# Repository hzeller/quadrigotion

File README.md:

Quadrigotion: Multiple Motor Drivers, one connector
============================================================

Often it is useful to have all the motor drivers needed for a machine
on a separate circuit board to be able to mount it to a heatsink or close
to the action. This is what this project is about.
The name **Quadrigotion** is a word amalgamated from 'Quadriga' (Four
horses powering a chariot) and 'Motion'.

Motivation for this project to have motor drivers easily replacable and
testable on my various 3D printers and CNC machines. Since I am also
[developing motion control software][BeagleG], I might have an unusual
high demand for this :)

The idea is to have a common connector type, described below, and various
implementations of that concept. The first implementation is using a TMC2660,
which is the 'big brother' of the more well-known TMC2100.

Other implementations are conceivable e.g. with Pololu modules, DRV8825, or
super high current and voltage drivers for heavy CNC machines.
Implementations can be super bare-bone and not use the SPI connection or
could be configured via SPI using a shift-register and digital potentiometers
if the chips can't be configured with SPI directly.
While the first Quadrigotion implementation happens to also have four motor
drivers, this could of course extend in the future.

The Connector
--------------

The digital input is provided with an IDC connector with 16 pins (2x8) or
20 pins (2x10).
It features a SPI bus to send configuration data and also read motor/driver
status (the actual protocol is of implementation-dependent, but they all can
share the same hardware interface).

| Desc               | Pin | Pin | Desc
|-------------------:|:---:|:---:|:-----------------------------
|               GND  |   1 |   2 | VCC (3.3V-5V)
| All Motors ~Enable |   3 |   4 | (not connected; reserved for fault-out)
|          ~CS (SPI) |   5 |   6 | CLK (SPI)
|         MISO (SPI) |   7 |   8 | MOSI (SPI)
|            Step #1 |   9 |  10 | Dir #1
|            Step #2 |  11 |  12 | Dir #2
|            Step #3 |  13 |  14 | Dir #3
|            Step #4 |  15 |  16 | Dir #4 -------- END IDC 16 variant
|            Step #5 |  17 |  18 | Dir #5
|            Step #6 |  19 |  20 | Dir #6 -------- END IDC 20 variant

It is easy to see that extending the driver count would just require a wider
IDC connector; the serial configuration interface can deal with any
number. A 16 pin IDC connector allows for 4 steppers, the next configuration
with 20 pins would allow for six drivers.

A single Enable-pin is provided that affects all drivers. This makes it easy
to wire up that signal directly e.g. for emergency buttons.
If more individual control of each driver is needed, this can be done via
the SPI connection.

The fast signals for each stepper, step and dir, are provided in
a parallel input with two lines per stepper.

A Quadrigotion connector has a single ChipSelect signal; multiple drivers
on each implementation have to share that bus, e.g. by internally being
organized as a shift register that latches when ~CS goes high again.

One pin (pin 4) is not connected yet, but it is reserved for fault detection
output (e.g stalling, overheating or over-current).

In an upcoming project, I'll build a breakout board to work with [BeagleG].

TMC2660 Implementation
----------------------

The first implementation is based on the TMC2660, a feature-rich motor driver
that can drive up to 4A (2.8A RMS). The 40mmx125mm PCB is a four layer board
which duals as heat conductor for cooling. Multiple M2.5 mounting holes allow
to firmly mount it to a heatsink and get even pressure to individual silicone
heatsink pads.
Power is provided via a 4-pin JST VH connector (3.96mm pitch),
circuit protected with an automotive ATC Mini 297 blade fuse.

You find the gerbers in the [fab/](./fab) directory. Board is also
[shared on OshPark]. Cave: since this is the very first version, no
testing has been done yet with a physical board.

[BeagleG]: https://github.com/hzeller/beagleg
[shared on OshPark]: https://oshpark.com/shared_projects/M0SQCRdL

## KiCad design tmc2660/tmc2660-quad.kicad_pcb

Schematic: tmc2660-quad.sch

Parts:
F1: Fuse; BladeFuse-Mini_Keystone-3586
J1: Power; JST_VH_B4PS-VH_2x4x3.96mm_Horizontal
J2: DataIn; IDC_Header_SMD_16pins
M0: Mount; MountingHole_2.7mm_M2.5
M1: Mount; MountingHole_2.7mm_M2.5_Pad

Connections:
/PowerIn: F1.2, J1.1, J1.2
CS: J2.5; also elsewhere on the board
DIR1: J2.10; also elsewhere on the board
DIR2: J2.12; also elsewhere on the board
DIR3: J2.14; also elsewhere on the board
DIR4: J2.16; also elsewhere on the board
GLOBAL_MISO: J2.7; also elsewhere on the board
GLOBAL_MOSI: J2.8; also elsewhere on the board
GND: J1.3, J1.4, J2.1, M1.1; also elsewhere on the board
SCLK: J2.6; also elsewhere on the board
STEP1: J2.9; also elsewhere on the board
STEP2: J2.11; also elsewhere on the board
STEP3: J2.13; also elsewhere on the board
STEP4: J2.15; also elsewhere on the board
VCC: J2.2; also elsewhere on the board
VMot: F1.1; also elsewhere on the board
~ENABLE: J2.3; also elsewhere on the board

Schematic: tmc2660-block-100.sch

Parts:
C100, C101: 10n; C_0603
C102, C103: 10u; C_1206; Voltage 50V; DigiKey 1276-6736-1-ND
C104, C106: 100n; C_0805; Voltage >= 16V; DigiKey 1276-2450-2-ND
C105: 100n; C_0805; Voltage 50V; DigiKey 1276-2450-2-ND
C107: 180u; CP_Radial_D8.0mm_P3.50mm; Voltage 35V; DigiKey 565-3911-ND
C108: 470n; C_0603; Voltage 16V
J100: 0R; R_0603
M100: Mount; MountingHole_2.7mm_M2.5
M101: Mount; MountingHole_2.7mm_M2.5_Pad
P100: Motor; JST_XH_B04B-XH-A_04x2.50mm_Straight
R100, R101: 0.075; R_2512; DigiKey CSRN2512FK75L0CT-ND
R102, R103: 10R; R_0603
U100: TMC2660; LQFP-44_10x10mm_Pitch0.8mm

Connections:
/TMC2660-100/A1: P100.2, U100.2 (OA1), U100.3 (OA1), U100.7 (OA1), U100.8 (OA1)
/TMC2660-100/A2: P100.1, U100.5 (OA2), U100.6 (OA2), U100.10 (OA2), U100.11 (OA2)
/TMC2660-100/B1: P100.3, U100.26 (OB1), U100.27 (OB1), U100.31 (OB1), U100.32 (OB1)
/TMC2660-100/B2: P100.4, U100.23 (OB2), U100.24 (OB2), U100.28 (OB2), U100.29 (OB2)
/TMC2660-100/BRA: R101.1, R103.2, U100.9 (BRA)
/TMC2660-100/BRB: R100.1, R102.1, U100.25 (BRB)
/TMC2660-100/VHS: C104.2, U100.35 (VHS)
/TMC2660-200/MISO: J100.2, U100.15 (MOSI); also elsewhere on the board
CS: U100.18 (~CS); also elsewhere on the board
DIR1: U100.41 (DIR); also elsewhere on the board
GLOBAL_MISO: U100.14 (MISO); also elsewhere on the board
GLOBAL_MOSI: J100.1; also elsewhere on the board
GND: C100.1, C101.2, C102.2, C103.2, C105.2, C106.2, C107.2, C108.2, M101.1, R100.2, R101.2, U100.1 (NC), U100.17 (GND), U100.21 (CLK), U100.39 (GND), U100.44 (GND); also elsewhere on the board
unnamed: C100.2, R102.2, U100.22 (SRB)
unnamed: C101.1, R103.1, U100.12 (SRA)
unnamed: C108.1, U100.13 (5VOUT)
SCLK: U100.16 (SCLK); also elsewhere on the board
STEP1: U100.42 (STEP); also elsewhere on the board
VCC: C106.1, U100.40 (VCC); also elsewhere on the board
VMot: C102.1, C103.1, C104.1, C105.1, C107.1, U100.4 (VSA), U100.30 (VSB), U100.33 (NC), U100.36 (VS); also elsewhere on the board
~ENABLE: U100.19 (~EN); also elsewhere on the board

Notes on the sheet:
Jumper on highest popuplated
Sense Resistors alternatively also with 100mOhm

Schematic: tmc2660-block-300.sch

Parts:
C300, C301: 10n; C_0603
C302, C303: 10u; C_1206; Voltage 50V; DigiKey 1276-6736-1-ND
C304, C306: 100n; C_0805; Voltage >= 16V; DigiKey 1276-2450-2-ND
C305: 100n; C_0805; Voltage 50V; DigiKey 1276-2450-2-ND
C307: 180u; CP_Radial_D8.0mm_P3.50mm; Voltage 35V; DigiKey 565-3911-ND
C308: 470n; C_0603; Voltage 16V
J300: 0R; R_0603
M300: Mount; MountingHole_2.7mm_M2.5
M301: Mount; MountingHole_2.7mm_M2.5_Pad
P300: Motor; JST_XH_B04B-XH-A_04x2.50mm_Straight
R300, R301: 0.075; R_2512; DigiKey CSRN2512FK75L0CT-ND
R302, R303: 10R; R_0603
U300: TMC2660; LQFP-44_10x10mm_Pitch0.8mm

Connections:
/TMC2660-300/A1: P300.2, U300.2 (OA1), U300.3 (OA1), U300.7 (OA1), U300.8 (OA1)
/TMC2660-300/A2: P300.1, U300.5 (OA2), U300.6 (OA2), U300.10 (OA2), U300.11 (OA2)
/TMC2660-300/B1: P300.3, U300.26 (OB1), U300.27 (OB1), U300.31 (OB1), U300.32 (OB1)
/TMC2660-300/B2: P300.4, U300.23 (OB2), U300.24 (OB2), U300.28 (OB2), U300.29 (OB2)
/TMC2660-300/BRA: R301.1, R303.2, U300.9 (BRA)
/TMC2660-300/BRB: R300.1, R302.1, U300.25 (BRB)
/TMC2660-300/MISO: U300.14 (MISO); also elsewhere on the board
/TMC2660-300/VHS: C304.2, U300.35 (VHS)
/TMC2660-400/MISO: J300.2, U300.15 (MOSI); also elsewhere on the board
CS: U300.18 (~CS); also elsewhere on the board
DIR3: U300.41 (DIR); also elsewhere on the board
GLOBAL_MOSI: J300.1; also elsewhere on the board
GND: C300.1, C301.2, C302.2, C303.2, C305.2, C306.2, C307.2, C308.2, M301.1, R300.2, R301.2, U300.1 (NC), U300.17 (GND), U300.21 (CLK), U300.39 (GND), U300.44 (GND); also elsewhere on the board
unnamed: C300.2, R302.2, U300.22 (SRB)
unnamed: C301.1, R303.1, U300.12 (SRA)
unnamed: C308.1, U300.13 (5VOUT)
SCLK: U300.16 (SCLK); also elsewhere on the board
STEP3: U300.42 (STEP); also elsewhere on the board
VCC: C306.1, U300.40 (VCC); also elsewhere on the board
VMot: C302.1, C303.1, C304.1, C305.1, C307.1, U300.4 (VSA), U300.30 (VSB), U300.33 (NC), U300.36 (VS); also elsewhere on the board
~ENABLE: U300.19 (~EN); also elsewhere on the board

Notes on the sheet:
Jumper on highest popuplated
Sense Resistors alternatively also with 100mOhm

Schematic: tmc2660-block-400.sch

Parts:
C400, C401: 10n; C_0603
C402, C403: 10u; C_1206; Voltage 50V; DigiKey 1276-6736-1-ND
C404, C406: 100n; C_0805; Voltage >= 16V; DigiKey 1276-2450-2-ND
C405: 100n; C_0805; Voltage 50V; DigiKey 1276-2450-2-ND
C407: 180u; CP_Radial_D8.0mm_P3.50mm; Voltage 35V; DigiKey 565-3911-ND
C408: 470n; C_0603; Voltage 16V
J400: 0R; R_0603
M400: Mount; MountingHole_2.7mm_M2.5
M401: Mount; MountingHole_2.7mm_M2.5_Pad
P400: Motor; JST_XH_B04B-XH-A_04x2.50mm_Straight
R400, R401: 0.075; R_2512; DigiKey CSRN2512FK75L0CT-ND
R402, R403: 10R; R_0603
U400: TMC2660; LQFP-44_10x10mm_Pitch0.8mm

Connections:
/TMC2660-400/A1: P400.2, U400.2 (OA1), U400.3 (OA1), U400.7 (OA1), U400.8 (OA1)
/TMC2660-400/A2: P400.1, U400.5 (OA2), U400.6 (OA2), U400.10 (OA2), U400.11 (OA2)
/TMC2660-400/B1: P400.3, U400.26 (OB1), U400.27 (OB1), U400.31 (OB1), U400.32 (OB1)
/TMC2660-400/B2: P400.4, U400.23 (OB2), U400.24 (OB2), U400.28 (OB2), U400.29 (OB2)
/TMC2660-400/BRA: R401.1, R403.2, U400.9 (BRA)
/TMC2660-400/BRB: R400.1, R402.1, U400.25 (BRB)
/TMC2660-400/MISO: U400.14 (MISO); also elsewhere on the board
/TMC2660-400/VHS: C404.2, U400.35 (VHS)
CS: U400.18 (~CS); also elsewhere on the board
DIR4: U400.41 (DIR); also elsewhere on the board
GLOBAL_MOSI: J400.1, J400.2, U400.15 (MOSI); also elsewhere on the board
GND: C400.1, C401.2, C402.2, C403.2, C405.2, C406.2, C407.2, C408.2, M401.1, R400.2, R401.2, U400.1 (NC), U400.17 (GND), U400.21 (CLK), U400.39 (GND), U400.44 (GND); also elsewhere on the board
unnamed: C400.2, R402.2, U400.22 (SRB)
unnamed: C401.1, R403.1, U400.12 (SRA)
unnamed: C408.1, U400.13 (5VOUT)
SCLK: U400.16 (SCLK); also elsewhere on the board
STEP4: U400.42 (STEP); also elsewhere on the board
VCC: C406.1, U400.40 (VCC); also elsewhere on the board
VMot: C402.1, C403.1, C404.1, C405.1, C407.1, U400.4 (VSA), U400.30 (VSB), U400.33 (NC), U400.36 (VS); also elsewhere on the board
~ENABLE: U400.19 (~EN); also elsewhere on the board

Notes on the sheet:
Jumper on highest popuplated
Sense Resistors alternatively also with 100mOhm

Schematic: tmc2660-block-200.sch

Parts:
C200, C201: 10n; C_0603
C202, C203: 10u; C_1206; Voltage 50V; DigiKey 1276-6736-1-ND
C204, C206: 100n; C_0805; Voltage >= 16V; DigiKey 1276-2450-2-ND
C205: 100n; C_0805; Voltage 50V; DigiKey 1276-2450-2-ND
C207: 180u; CP_Radial_D8.0mm_P3.50mm; Voltage 35V; DigiKey 565-3911-ND
C208: 470n; C_0603; Voltage 16V
J200: 0R; R_0603
M200: Mount; MountingHole_2.7mm_M2.5
M201: Mount; MountingHole_2.7mm_M2.5_Pad
P200: Motor; JST_XH_B04B-XH-A_04x2.50mm_Straight
R200, R201: 0.075; R_2512; DigiKey CSRN2512FK75L0CT-ND
R202, R203: 10R; R_0603
U200: TMC2660; LQFP-44_10x10mm_Pitch0.8mm

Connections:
/TMC2660-200/A1: P200.2, U200.2 (OA1), U200.3 (OA1), U200.7 (OA1), U200.8 (OA1)
/TMC2660-200/A2: P200.1, U200.5 (OA2), U200.6 (OA2), U200.10 (OA2), U200.11 (OA2)
/TMC2660-200/B1: P200.3, U200.26 (OB1), U200.27 (OB1), U200.31 (OB1), U200.32 (OB1)
/TMC2660-200/B2: P200.4, U200.23 (OB2), U200.24 (OB2), U200.28 (OB2), U200.29 (OB2)
/TMC2660-200/BRA: R201.1, R203.2, U200.9 (BRA)
/TMC2660-200/BRB: R200.1, R202.1, U200.25 (BRB)
/TMC2660-200/MISO: U200.14 (MISO); also elsewhere on the board
/TMC2660-200/VHS: C204.2, U200.35 (VHS)
/TMC2660-300/MISO: J200.2, U200.15 (MOSI); also elsewhere on the board
CS: U200.18 (~CS); also elsewhere on the board
DIR2: U200.41 (DIR); also elsewhere on the board
GLOBAL_MOSI: J200.1; also elsewhere on the board
GND: C200.1, C201.2, C202.2, C203.2, C205.2, C206.2, C207.2, C208.2, M201.1, R200.2, R201.2, U200.1 (NC), U200.17 (GND), U200.21 (CLK), U200.39 (GND), U200.44 (GND); also elsewhere on the board
unnamed: C200.2, R202.2, U200.22 (SRB)
unnamed: C201.1, R203.1, U200.12 (SRA)
unnamed: C208.1, U200.13 (5VOUT)
SCLK: U200.16 (SCLK); also elsewhere on the board
STEP2: U200.42 (STEP); also elsewhere on the board
VCC: C206.1, U200.40 (VCC); also elsewhere on the board
VMot: C202.1, C203.1, C204.1, C205.1, C207.1, U200.4 (VSA), U200.30 (VSB), U200.33 (NC), U200.36 (VS); also elsewhere on the board
~ENABLE: U200.19 (~EN); also elsewhere on the board

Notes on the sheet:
Jumper on highest popuplated
Sense Resistors alternatively also with 100mOhm

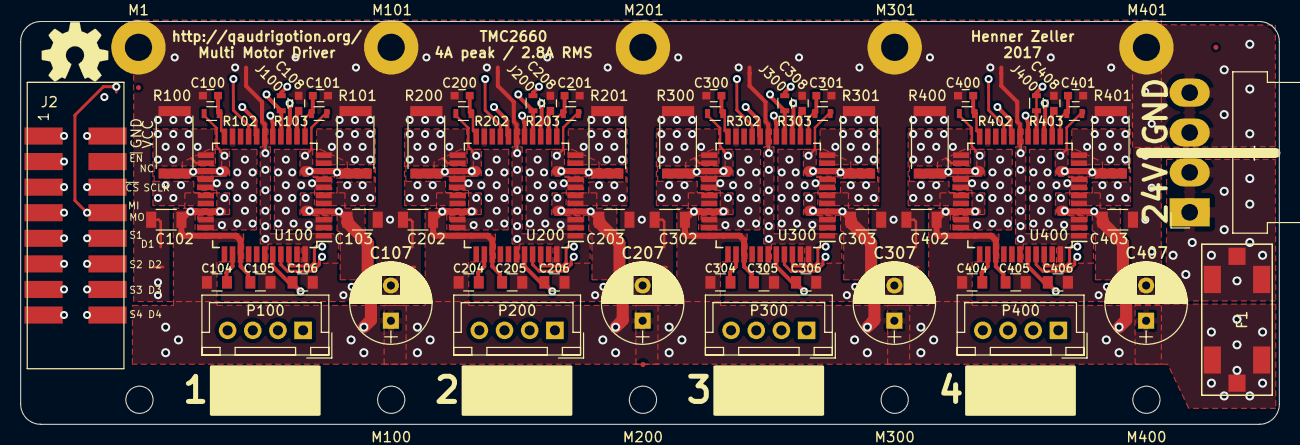
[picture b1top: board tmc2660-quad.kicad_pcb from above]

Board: 4 copper layers, 125.0 x 40.0 mm, 77 parts (0 on the bottom side), 60 nets.

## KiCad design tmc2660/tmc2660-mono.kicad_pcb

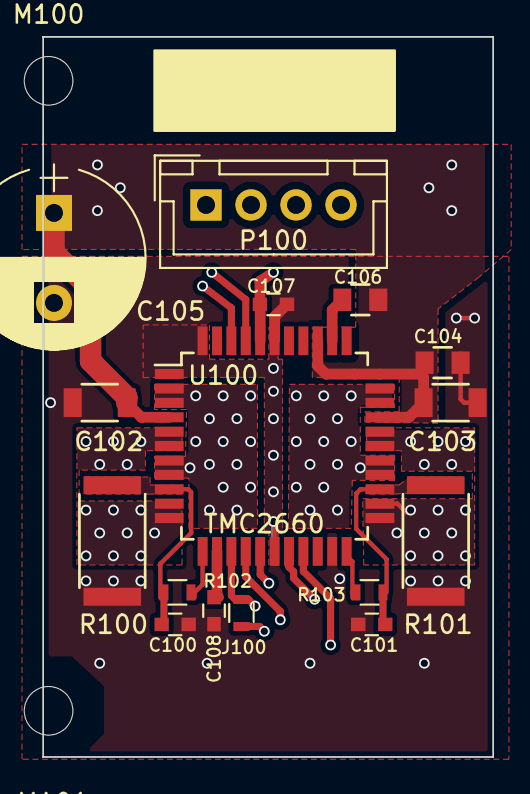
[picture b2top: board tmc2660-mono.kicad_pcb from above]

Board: 4 copper layers, 25.0 x 40.0 mm, 18 parts (0 on the bottom side), 14 nets.

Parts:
C100, C101: 10n; C_0603
C102, C103: 10u; C_1206
C104, C106: 100n; C_0805
C105: 100u; CP_Radial_D10.0mm_P5.00mm
C107: 100n; C_0603
C108: 470n; C_0603
J100: 0R; R_0603
M100, M101: Mount; MountingHole_2.7mm_M2.5
P100: Motor; JST_XH_B04B-XH-A_04x2.50mm_Straight
R100, R101: 0.075; R_2512
R102, R103: 10R; R_0603
U100: TMC2660; LQFP-44_10x10mm_Pitch0.8mm

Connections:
/TMC2660-Block/A1: P100.2, U100.2, U100.3, U100.7, U100.8
/TMC2660-Block/A2: P100.1, U100.5, U100.6, U100.10, U100.11
/TMC2660-Block/B1: P100.3, U100.26, U100.27, U100.31, U100.32
/TMC2660-Block/B2: P100.4, U100.23, U100.24, U100.28, U100.29
/TMC2660-Block/BRA: C100.2, R100.1, R102.2, U100.9
/TMC2660-Block/BRB: C101.1, R101.1, R103.1, U100.25
/TMC2660-Block/MISO: J100.2, U100.14
GND: C100.1, C101.2, C102.2, C103.2, C104.2, C105.2, C107.2, C108.2, R100.2, R101.2, U100.1, U100.17, U100.21, U100.39, U100.44
unnamed: C106.2, U100.35
unnamed: C108.1, U100.13
unnamed: R102.1, U100.12
unnamed: R103.2, U100.22
VCC: C107.1, U100.40
VMot: C102.1, C103.1, C104.1, C105.1, C106.1, U100.4, U100.30, U100.33, U100.36

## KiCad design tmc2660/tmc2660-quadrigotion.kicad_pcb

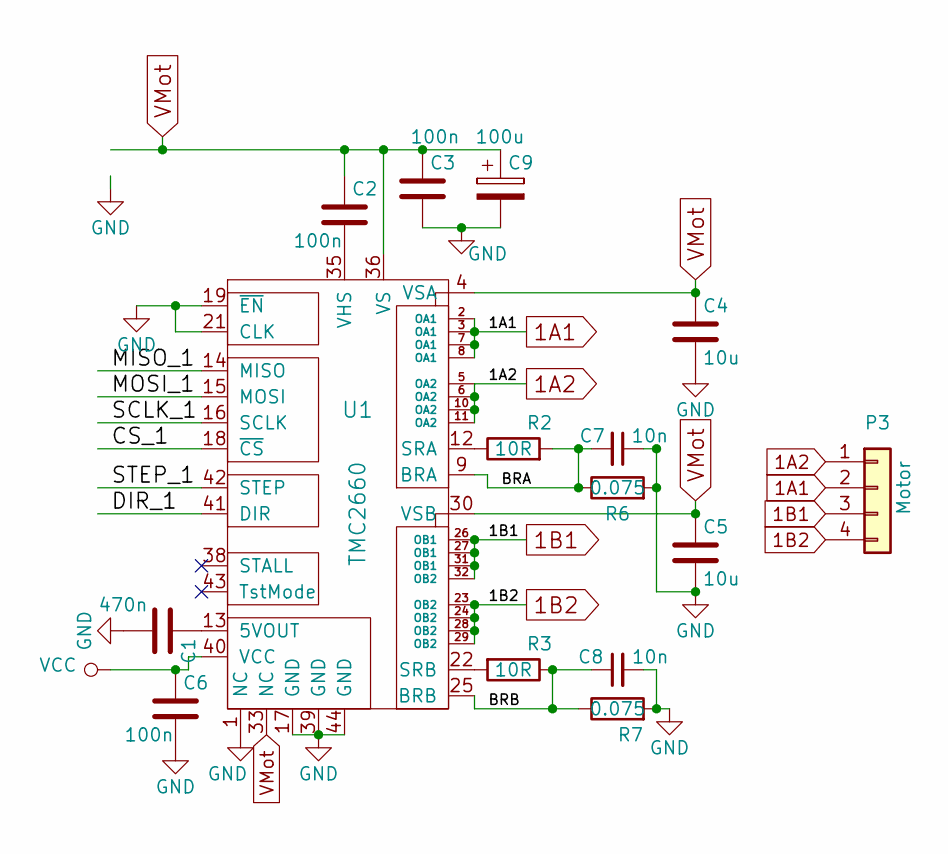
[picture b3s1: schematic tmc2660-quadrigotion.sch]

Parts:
C1: 470n; C_0603
C2, C3: 100n; C_0805
C4, C5: 10u; C_1206
C6: 100n; C_0603
C7, C8: 10n; C_0603
C9: 100u; CP_Radial_D10.0mm_P5.00mm
P3: Motor; JST_VH_B4P-VH_4x3.96mm_Vertical
R2, R3: 10R; R_0603
R6, R7: 0.075; R_2512
U1: TMC2660; LQFP-44_10x10mm_Pitch0.8mm

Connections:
1A1: P3.2, U1.2 (OA1), U1.3 (OA1), U1.7 (OA1), U1.8 (OA1)
1A2: P3.1, U1.5 (OA2), U1.6 (OA2), U1.10 (OA2), U1.11 (OA2)
1B1: P3.3, U1.26 (OB1), U1.27 (OB1), U1.31 (OB1), U1.32 (OB2)
1B2: P3.4, U1.23 (OB2), U1.24 (OB2), U1.28 (OB2), U1.29 (OB2)
/BRA: C7.2, R2.2, R6.1, U1.9 (BRA)
/BRB: C8.1, R3.1, R7.1, U1.25 (BRB)
/CS_1: U1.18 (~CS)
/DIR_1: U1.41 (DIR)
/MISO_1: U1.14 (MISO)
/MOSI_1: U1.15 (MOSI)
/SCLK_1: U1.16 (SCLK)
/STEP_1: U1.42 (STEP)
GND: C1.2, C3.2, C4.2, C5.2, C6.2, C7.1, C8.2, C9.2, R6.2, R7.2, U1.1 (NC), U1.17 (GND), U1.19 (~EN), U1.21 (CLK), U1.39 (GND), U1.44 (GND)
unnamed: C1.1, U1.13 (5VOUT)
unnamed: C2.2, U1.35 (VHS)
unnamed: R2.1, U1.12 (SRA)
unnamed: R3.2, U1.22 (SRB)
VCC: C6.1, U1.40 (VCC)
VMot: C2.1, C3.1, C4.1, C5.1, C9.1, U1.4 (VSA), U1.30 (VSB), U1.33 (NC), U1.36 (VS)

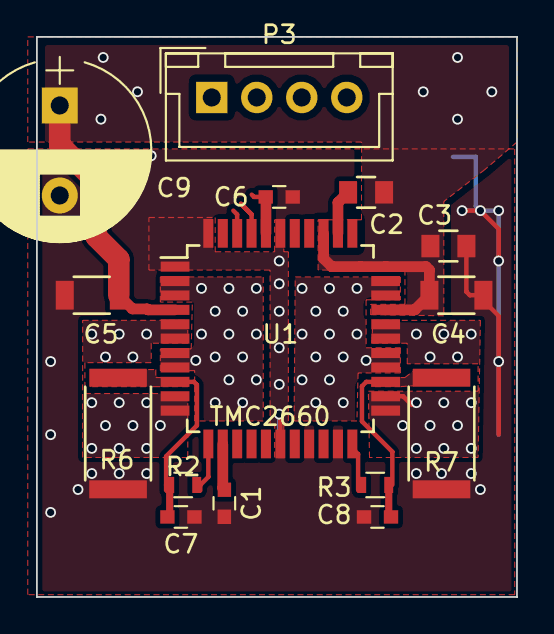
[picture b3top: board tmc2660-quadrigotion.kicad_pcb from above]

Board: 4 copper layers, 26.7 x 31.1 mm, 15 parts (0 on the bottom side), 13 nets.

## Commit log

2017-11-12 Starting by preparing the tmc2660 breakout to be used in sequence.
    o Mostly preparing that the motor voltage carrying traces enter and leave
    at the same position right and left of the board.
    o No logical connection yet: Step/Dir and SPI bus will be routed in an
    inner layer.
    o (it is not clear yet if it will be simple to copy/paste a template
    board design easily; but we'll make it work)
2017-11-12 Use smaller connector. JST XH is sufficient for the currents at hand, no need for JST VH
    o Also: size adaption. The smaller connector allows to make the board a little
    narrower.
    o Add copper pour for VMOT.
2017-11-12 Prepare the inner layers.
    o Mostly one layer GND and VMOT.
    o Have copper fills for all the heatsinking regions to create a good
    heat-conductive connection top to bottom.
    o One layer leave mostly free for signals (except VMOT which is
    somewhat out of the way anyway and the heatsinking zones).
    o No signals routed yet (probably only going to happen once the
2017-11-13 Fix mis-labelled pin in schematic symbol.
2017-11-13 Better silk-screen position of some caps.
2017-11-13 Put new symbol in cache.
2017-11-13 Give board a simpler name: tmc2660-quad
2017-11-13 Add Makefile for gerber generation.
2017-11-13 Arrange ceramic VMOT caps more symmetrically.
2017-11-13 Add a VCC connecting bar.
2017-11-14 Wire up SPI in signal layer; prepare Step/Dir.
2017-11-14 Add mounting holes; trim sizes to 'round' values.
    o Size of board is 25mmx40mm
    o Distance M2.5 mounting holes: 35mm
    o Width needs to be a 'round' number so that replicated
    drivers have properly distanted mounting holes.
2017-11-14 Allow motor voltage around mounting hole in inner layers.
    Outer layers should not carry motor voltage near the mounting screw
    in case the soldermask gets damaged. Inner layers are ok and provide
    a an additional nice low-impedance path.
2017-11-14 Move some designator markings; Make screws frame chip.
    Also, add a filled silkscreen square for manual sharpie markings.
    ... alas, the gerber export for that seems to not work yet in the
    KiCAD version I am using.
2017-11-14 Rename the building block for the eventual quad tmc2660-mono.
2017-11-14 Adapt Makefille for the mono conversion.
2017-11-14 Adapt some vias around the SPI connect to fix a gap in the TopCu copper pour.
2017-11-15 Lock mounting holes.
2017-11-15 Schematic lib update.
2017-11-15 Add ~ENABLE to the bus.
2017-11-15 First transition into hierachical sheets.
2017-11-16 More sensible annotations, starting in the 100 range.
2017-11-16 Numbering scheme: have U1 be U100.
2017-11-16 J1 -> J100
2017-11-18 More preparation for cloning.
2017-11-18 Move template to separate dir. Adapt KiCAD 5.0 symbol lib.
2017-11-18 Basic Schematic with cloned hierarchical sub-schematics for each block.
2017-11-18 Consistently name first block TMC2660-100 in schematic and pcb.
2017-11-18 Prepare PCB cloning with layout-cloner.
2017-11-18 Add connectors.
2017-11-18 Start with MOSI on the right; turn around board.
    - Turn template board upside down, so that the IDC data connector
    can be on the left, and the motor outputs are marked 1..4 seen
    from there.
    - Instead of the last chip returning its output, we have it
    receive the MOSI. That way, the leftmost chip is naturally
    number 1 in the sequence of the shift register.
2017-11-19 Wire up quad according to new MISO/MOSI sequence.
    - Also, add basic STEP/DIR and a capacitor.
2017-11-19 Initial version of PCB with cloned template components.
2017-11-19 Add leftmost screw holes; Move IDC connector down.
2017-11-19 Establish more conservative design rules.
2017-11-19 More conservative design rules in quad.
2017-11-19 Routing of Step/Dir signals with new design rules.
2017-11-19 Fix Makefile to refer to current file.
2017-11-19 Fix gap in copper pour.
2017-11-19 Add a fuse.
2017-11-19 Add labels.
    o White label areas under connectors for the user to write
    the logical axis with sharpie.
    o gitversion, github address etc.
2017-11-19 Add digital connector legend. Round board corners.
2017-11-19 Add a README.
2017-11-19 Template: make work with larger annular ring sizes.
2017-11-19 More easily fabricatable design rules: 0.8mm via/0.4mm drill.
2017-11-19 Move bottom silkscreen a little ouf of the way of vias.
    o Also: larger vias in the general power input area.
2017-11-19 Add fab output; update README.
2017-11-20 Fix some traces that unnecessarily have been pushed through copper fills.
2017-11-21 Make some copper areas flow better.
2017-11-21 Manufacturability: some board houses want 0.2mm/8mil structure size for 70um/2oz copper.
2017-11-22 Replace polygons with zones that are less broken objects.
2017-11-22 Move template to a somewhat sane (100,100) origin.
2017-11-22 layout-cloner: make the transformation a general function parametrized by clone index.
2017-11-24 More DFM: choose more common physical capacitor sizes.
    o Capacitors in the 100-150uF and 35-50V range are typically 8mm dia.
    o Choose all 100nF same size. Even for 50V, there are 0603 available.
    o Properly connect the 10nF smoothing capacitor for shunt feedback
    voltage (was connected to GND on the wrong side).
2017-11-24 Rename local *.pretty to project name.
2017-11-24 Add 30A 9.5mm pitch 2 terminal screw terminal OSTYK51102030
2017-11-24 Rename screw terminal to full vendor ID
2017-11-25 Proper rename of terminal block component id in file.
2017-11-26 Tweaks to inner ground layer and top motor voltage zone.
2017-11-26 Update tmc2660-quad with new template.
    o Start out with a tmc2660-quad-baseline that is filled
    in with zones and tracks from the template.
    o The separation from baseline and template allows faster
    updates later.
2017-11-26 Remove comment zone from template.
    o We're not requiring anymore to have a comment zone around the
    relevant parts, as we now separate template from board to be
    edited.
2017-11-26 Update layout-cloner.py script to read from separate template file.
    o Unlike the previous approach, that contained the template as part
    of the baseline board, a layout is now created from a separate
    template file and a baseline file that then result in a combined board.
    o Mark all copied tracks/zones/drawings with a magic timestamp so
    that it is possible to later fish these out.
    o Provide clean-magic-tstamp.py to allow creating a new baseline
2017-11-26 Add bottom silkscreen.
2017-11-26 Update fab file.
2017-11-26 Add front silkscreen. Re-add center fiducial.
    o Front silkscreen and center fiducial got lost in the previous
    steps.
    o Re-add in the baseline file and re-generate the final file.
2017-11-27 Larger cooling area in the In2 inner layer for A2/B2 pads.
2017-11-27 GND plane around Step/Dir. Tighter routing of Step/Dir.
2017-11-27 Better choice of common component size; GND mounting hole.
    o 50V ceramic capacitors are easier and cheaper to get in 0805
    o Mounting holes near GND should be grounded to have a known
    potential for the heatsink.
2017-11-27 Use simple GND screw-mounting hole instead of with vias.
2017-11-27 Integrate grounded mounting hole.
2017-11-27 Silk screen: http://quadrigotion.org/ on front; github ref on back.
2017-11-27 Mounting hole: simplify zone connect.
2017-11-27 Simplify GND mount hole.
2017-11-27 Update rendering.
2017-11-27 Update the right picture.
2017-11-28 More cooling for input VMOT and output current for bondwire cooling.
2017-11-28 Keep vias out of pads.
2017-11-30 Tweaking vias around vmot pins.
2017-11-30 Add signal description also on front silk-screen.
    o In template: move a designator out of the way to not collide with that
    description.
2017-11-30 Update Gerbers.
2017-12-01 Use surface-mount IDC connector for easier PCB heatsink mount.
2017-12-05 Thicker silkscreen text on IDC.
2017-12-05 Improve readability designators.
    o Larger font if possible.
    o Avoid printing over vias if possible.
2017-12-06 Move VMOT 100nF input stabilisator for VHS voltage regulator close to pin.
    o Re-number the 100nF capacitors that they show up in an increasing numbers
    o Use opportunity to move silkscreen of 10uF capacitors out of via's harms way.
2017-12-06 Update rendering and fab-files.
2017-12-06 Update OshPark link.
2017-12-06 Move VCC via between motor output zones.
2017-12-06 Update fab.
2017-12-06 Update fab files.
2017-12-06 Center electrolytic capacitor designator.
2017-12-06 Update fab, rendering and OshPark link.
2017-12-16 Fix data direction of some direction labels :)
2018-08-20 Add schematic PDF.
